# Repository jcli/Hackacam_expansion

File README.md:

Hackacam_expansion
==================

Simple expansion module for the Hackacam platform.

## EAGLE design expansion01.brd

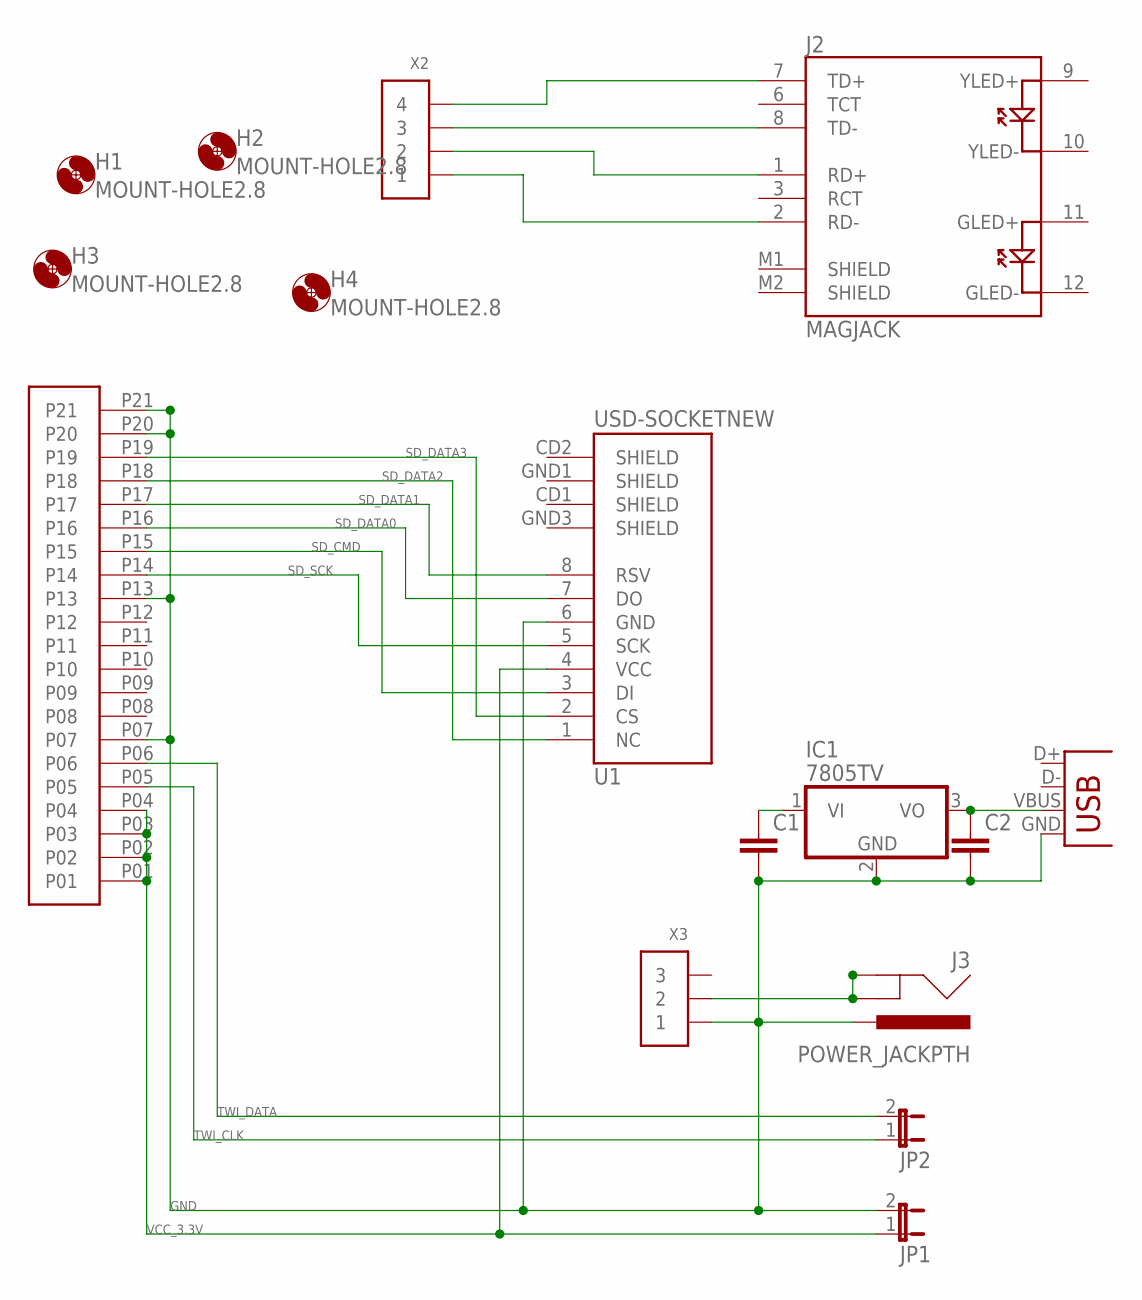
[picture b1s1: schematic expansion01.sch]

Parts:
C1, C2: C-EUC0402; C0402
H1, H2, H3, H4: MOUNT-HOLE2.8; 2,8
IC1: 7805TV; TO220V
J2: MAGJACK
J3: POWER_JACKPTH; POWER_JACK_PTH
JP1, JP2: JUMPER-2PTH; 1X02
JP3: USB-A-S
U1: USD-SOCKETNEW; MICRO-SD-SOCKET-PP
U$1: FH26-21S-0.3SHW_05; ZIF21
X2: CONN_4-1-53261; PB-53261-04
X3: CONN_3-1-53261; PB-53261-03

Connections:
GND: C1.2, C2.2, IC1.2 (GND), J3.PWR, JP1.2, JP3.GND, U1.6 (GND), U$1.P07, U$1.P13, U$1.P20, U$1.P21, X3.1
unnamed: C2.1, IC1.3 (VO), JP3.VBUS
unnamed: C1.1, IC1.1 (VI)
unnamed: J2.7 (TD+), X2.4
unnamed: J2.8 (TD-), X2.3
unnamed: J2.1 (RD+), X2.2
unnamed: J2.2 (RD-), X2.1
SD_CMD: U1.3 (DI), U$1.P15
SD_DATA0: U1.7 (DO), U$1.P16
SD_DATA1: U1.8 (RSV), U$1.P17
SD_DATA2: U1.1 (NC), U$1.P18
SD_DATA3: U1.2 (CS), U$1.P19
SD_SCK: U1.5 (SCK), U$1.P14
TWI_CLK: JP2.1, U$1.P05
TWI_DATA: JP2.2, U$1.P06
VCC_3.3V: JP1.1, U1.4 (VCC), U$1.P01, U$1.P02, U$1.P03, U$1.P04
VCC_12V: J3.GND, J3.GNDBREAK, X3.2

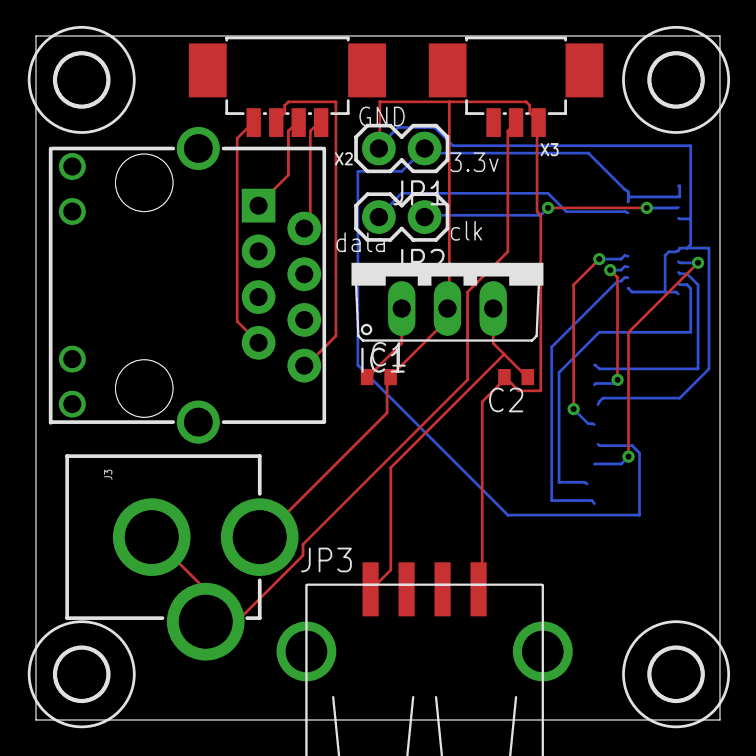
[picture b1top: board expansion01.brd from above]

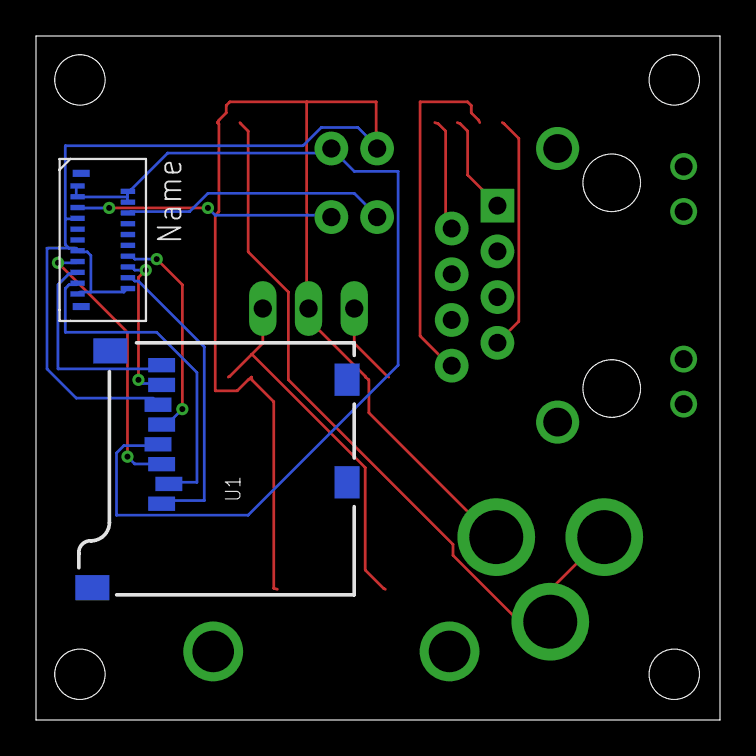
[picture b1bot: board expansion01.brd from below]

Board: 2 copper layers, 38.0 x 38.0 mm, 16 parts (2 on the bottom side), 17 nets.

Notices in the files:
parts and their libraries:
SparkFun-Connectors: Licensing: CC v3.0 Share-Alike You are welcome to use this library for commercial purposes.
